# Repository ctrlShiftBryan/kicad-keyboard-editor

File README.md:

# kicad-keyboard-editor README

This is the README for your extension "kicad-keyboard-editor". After writing up a brief description, we recommend including the following sections.

## Features

Describe specific features of your extension including screenshots of your extension in action. Image paths are relative to this README file.

For example if there is an image subfolder under your extension project workspace:

\!\[feature X\]\(images/feature-x.png\)

> Tip: Many popular extensions utilize animations. This is an excellent way to show off your extension! We recommend short, focused animations that are easy to follow.

## Requirements

If you have any requirements or dependencies, add a section describing those and how to install and configure them.

## Extension Settings

Include if your extension adds any VS Code settings through the `contributes.configuration` extension point.

For example:

This extension contributes the following settings:

* `myExtension.enable`: enable/disable this extension
* `myExtension.thing`: set to `blah` to do something

## Known Issues

Calling out known issues can help limit users opening duplicate issues against your extension.

## Release Notes

Users appreciate release notes as you update your extension.

### 1.0.0

Initial release of ...

### 1.0.1

Fixed issue #.

### 1.1.0

Added features X, Y, and Z.

-----------------------------------------------------------------------------------------------------------
## Following extension guidelines

Ensure that you've read through the extensions guidelines and follow the best practices for creating your extension.

* [Extension Guidelines](https://code.visualstudio.com/api/references/extension-guidelines)

## Working with Markdown

**Note:** You can author your README using Visual Studio Code.  Here are some useful editor keyboard shortcuts:

* Split the editor (`Cmd+\` on macOS or `Ctrl+\` on Windows and Linux)
* Toggle preview (`Shift+CMD+V` on macOS or `Shift+Ctrl+V` on Windows and Linux)
* Press `Ctrl+Space` (Windows, Linux) or `Cmd+Space` (macOS) to see a list of Markdown snippets

### For more information

* [Visual Studio Code's Markdown Support](http://code.visualstudio.com/docs/languages/markdown)
* [Markdown Syntax Reference](https://help.github.com/articles/markdown-basics/)

**Enjoy!**

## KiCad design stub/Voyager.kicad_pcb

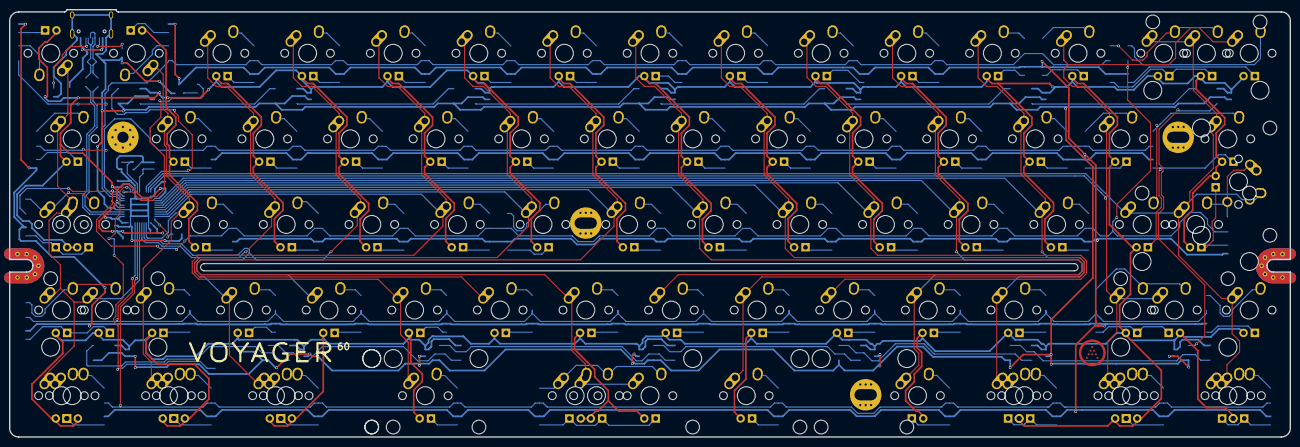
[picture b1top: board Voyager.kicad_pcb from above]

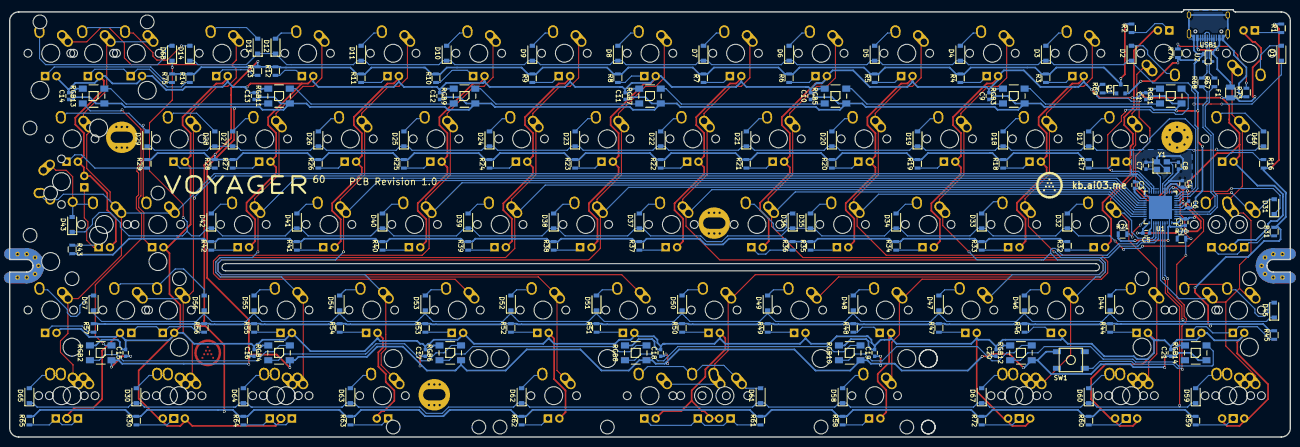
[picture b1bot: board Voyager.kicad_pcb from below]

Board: 2 copper layers, 285.0 x 95.1 mm, 261 parts (181 on the bottom side), 182 nets.

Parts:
C1, C3, C4, C5, C9, C10, C11, C12, C13, C14, C15, C16, C17, C18, C19, C20, C21: 0.1uF; C_0603
C2: 10uF; C_0603
C6: 1uF; C_0603
C7, C8: 22pF; C_0603
D1, D2, D3, D4, D5, D6, D7, D8, D9, D10, D11, D12, D13, D14, D16, D17, D18, D19, D20, D21, D22, D23, D24, D25, D26, D27, D28, D29, D30, D31, D32, D33, D34, D35, D36, D37, D38, D39, D40, D41, D42, D43, D44, D45, D46, D47, D48, D49, D50, D51, D52, D53, D54, D55, D56, D57, D58, D59, D60, D61, D62, D63, D64, D65, D67, D68: SOD-123; D_SOD-123
F1: 500mA; Fuse_SMD1206_Reflow
K_#1, K_#2, K_#3, K_#4, K_#5, K_#6, K_#7, K_#8, K_#9, K_#10: MX-1U
K_'1: MX-1U
K_,1: MX-1U
K_-1: MX-1U
K_.1: MX-1U
K_/1: MX-1U
K_;1: MX-1U
K_=1: MX-1U
K_A1: MX-1U
K_ALT1: MX-1.25U
K_ALT2: MX-1.5U; MX-1.5U-FLIPPED
K_B1: MX-1U
K_BACK1: MX-2U
K_C1: MX-1U
K_CAPS1: MX-1.75U
K_CAPS2: MX-1.25U; MX-1.25U-FLIPPED
K_CTRL1: MX-1.25U
K_CTRL2: MX-1.5U; MX-1.5U-FLIPPED
K_D1: MX-1U
K_E1: MX-1U
K_ENTER1: MX-2.25U
K_ENTER2: MX-ISO; MX-ISO-ReversedStabilizers
K_ESC1: MX-1U
K_F1: MX-1U
K_G1: MX-1U
K_H1: MX-1U
K_I1: MX-1U
K_J1: MX-1U
K_K1: MX-1U
K_L1: MX-1U
K_M1: MX-1U
K_N1: MX-1U
K_O1: MX-1U
K_P1: MX-1U
K_Q1: MX-1U
K_R1: MX-1U
K_RALT2: MX-1.25U; MX-1.25U-FLIPPED
K_RALT3: MX-1.5U; MX-1.5U-FLIPPED
K_RCTRL2: MX-1.25U
K_RCTRL3: MX-1.5U; MX-1.5U-FLIPPED
K_RMENU2: MX-1.25U; MX-1.25U-FLIPPED
K_RSHIFT1: MX-2.75U; MX-2.75U-FLIPPED
K_RWIN2: MX-1.25U
K_RWIN3: MX-1U
K_S1: MX-1U
K_SBACK1, K_SBACK2: MX-1U
K_SHIFT1: MX-2.25U
K_SHIFT2: MX-1.25U
K_SHIFT3: MX-1U
K_SPACE1: MX-7U; MX-7U-ReversedStabilizers
K_SPACE2: MX-6.25U; MX-6.25U-ReversedStabilizers
K_SPACE3: MX-2.25U; MX-2.25U-ReversedStabilizers
K_SPACE4: MX-2.75U; MX-2.75U-ReversedStabilizers
K_SPACE5: MX-1.25U; MX-1.25U-FLIPPED
K_SRSHIFT1: MX-1.75U
K_SRSHIFT2: MX-1U
K_T1: MX-1U
K_TAB1: MX-1.5U
K_U1: MX-1U
K_V1: MX-1U
K_W1: MX-1U
K_WIN1: MX-1.25U
K_WIN2: MX-1U; MX-1U-FLIPPED
K_X1: MX-1U
K_Y1: MX-1U
K_Z1: MX-1U
K_[1: MX-1U
K_\1: MX-1.5U
K_\2: MX-1U
K_]1: MX-1U
Q1: 2N7002; SOT-23
R1, R2, R3, R4, R5, R6, R7, R8, R9, R10, R11, R12, R13, R14, R16, R17, R18, R19, R20, R21, R22, R23, R24, R25, R26, R27, R28, R29, R30, R31, R32, R33, R34, R35, R36, R37, R38, R39, R40, R41, R42, R43, R44, R45, R46, R47, R48, R49, R50, R51, R52, R53, R54, R55, R56, R57, R58, R59, R60, R61, R62, R63, R64, R65, R69, R71, R72, R75: 1k; R_0805
R67, R68: 22; R_0805
R70: 10k; R_0805
R73, R74: 5.1k; R_0805
RGB1, RGB2, RGB3, RGB4, RGB5, RGB6, RGB7, RGB8, RGB9, RGB10, RGB11, RGB12, RGB13, RGB14: WS2812B
SW1: 5.2x5.2mm; SKQG-1155865
U1: ATmega32U4-MU; QFN-44-1EP_7x7mm_Pitch0.5mm
U2: PRTR5V0U2X; SOT143B
USB1: HRO-TYPE-C-31-M-12; HRO-TYPE-C-31-M-12-Assembly
Y1: 16Mhz; Crystal_SMD_3225-4pin_3.2x2.5mm

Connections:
+5V: C1.2, C2.2, C3.2, C4.2, C5.2, C9.2, C10.2, C11.2, C12.2, C13.2, C14.2, C15.2, C16.2, C17.2, C18.2, C19.2, C20.2, C21.2, F1.1, K_#1.3, K_#2.3, K_#3.3, K_#4.3, K_#5.3, K_#6.3, K_#7.3, K_#8.3, K_#9.3, K_#10.3, K_'1.3, K_,1.3, K_-1.3, K_.1.3, K_/1.3, K_;1.3, K_=1.3, K_A1.3, K_ALT1.3, K_ALT2.3, K_B1.3, K_BACK1.3, K_C1.3, K_CAPS1.3, K_CAPS2.3, K_CTRL1.3, K_CTRL2.3, K_D1.3, K_E1.3, K_ENTER1.3, K_ENTER2.3, K_ESC1.3, K_F1.3, K_G1.3, K_H1.3, K_I1.3, K_J1.3, K_K1.3, K_L1.3, K_M1.3, K_N1.3, K_O1.3, K_P1.3, K_Q1.3, K_R1.3, K_RALT2.3, K_RALT3.3, K_RCTRL2.3, K_RCTRL3.3, K_RMENU2.3, K_RSHIFT1.3, K_RWIN2.3, K_RWIN3.3, K_S1.3, K_SBACK1.3, K_SBACK2.3, K_SHIFT1.3, K_SHIFT2.3, K_SHIFT3.3, K_SPACE1.3, K_SPACE2.3, K_SPACE3.3, K_SPACE4.3, K_SPACE5.3, K_SRSHIFT1.3, K_SRSHIFT2.3, K_T1.3, K_TAB1.3, K_U1.3, K_V1.3, K_W1.3, K_WIN1.3, K_WIN2.3, K_X1.3, K_Y1.3, K_Z1.3, K_[1.3, K_\1.3, K_\2.3, K_]1.3, R70.1, RGB1.1, RGB2.1, RGB3.1, RGB4.1, RGB5.1, RGB6.1, RGB7.1, RGB8.1, RGB9.1, RGB10.1, RGB11.1, RGB12.1, RGB13.1, RGB14.1, U1.2, U1.7, U1.14, U1.24, U1.34, U1.44
COL0: K_CAPS1.1, K_CAPS2.2, K_CTRL1.1, K_CTRL2.1, K_ESC1.1, K_SHIFT1.1, K_SHIFT2.1, K_TAB1.1, U1.39
COL1: K_#1.1, K_A1.1, K_Q1.1, K_SHIFT3.1, K_WIN1.1, K_WIN2.1, U1.36
COL2: K_#2.1, K_ALT1.1, K_ALT2.1, K_S1.1, K_W1.1, K_Z1.1, U1.38
COL3: K_#3.1, K_D1.1, K_E1.1, K_X1.1, U1.37
COL4: K_#4.1, K_C1.1, K_F1.1, K_R1.1, K_SPACE3.1, U1.32
COL5: K_#5.1, K_G1.1, K_T1.1, K_V1.1, U1.31
COL6: K_#6.1, K_B1.1, K_H1.1, K_SPACE1.1, K_SPACE2.1, K_SPACE5.2, K_Y1.1, U1.30
COL7: K_#7.1, K_J1.1, K_N1.1, K_U1.1, U1.29
COL8: K_#8.1, K_I1.1, K_K1.1, K_M1.1, K_SPACE4.1, U1.28
COL9: K_#9.1, K_,1.1, K_L1.1, K_O1.1, U1.27
COL10: K_#10.1, K_.1.1, K_;1.1, K_P1.1, K_RALT2.1, U1.26
COL11: K_'1.1, K_-1.1, K_/1.1, K_RALT3.1, K_RWIN2.1, K_[1.1, U1.25
COL12: K_=1.1, K_RMENU2.1, K_RSHIFT1.1, K_RWIN3.1, K_SBACK2.1, K_SRSHIFT1.1, K_]1.1, U1.22
COL13: K_BACK1.1, K_ENTER1.1, K_ENTER2.1, K_RCTRL2.1, K_RCTRL3.1, K_SBACK1.1, K_SRSHIFT2.1, K_\1.1, K_\2.1, U1.21
D+: R68.1, U1.4
D-: R67.1, U1.3
GND: C1.1, C2.1, C3.1, C4.1, C5.1, C6.2, C7.2, C8.2, C9.1, C10.1, C11.1, C12.1, C13.1, C14.1, C15.1, C16.1, C17.1, C18.1, C19.1, C20.1, C21.1, Q1.2, R71.1, R73.1, R74.1, RGB1.3, RGB2.3, RGB3.3, RGB4.3, RGB5.3, RGB6.3, RGB7.3, RGB8.3, RGB9.3, RGB10.3, RGB11.3, RGB12.3, RGB13.3, RGB14.3, SW1.1, U1.5, U1.15, U1.23, U1.35, U1.43, U1.45, U2.1, USB1.1, USB1.12, USB1.13, Y1.2, Y1.4
LEDGND: Q1.3, R1.2, R2.2, R3.2, R4.2, R5.2, R6.2, R7.2, R8.2, R9.2, R10.2, R11.2, R12.2, R13.2, R14.2, R16.2, R17.2, R18.2, R19.2, R20.2, R21.2, R22.2, R23.2, R24.2, R25.2, R26.2, R27.2, R28.2, R29.2, R30.2, R31.2, R32.2, R33.2, R34.2, R35.2, R36.2, R37.2, R38.2, R39.2, R40.2, R41.2, R42.2, R43.2, R44.2, R45.2, R46.2, R47.2, R48.2, R49.2, R50.2, R51.2, R52.2, R53.2, R54.2, R55.2, R56.2, R57.2, R58.2, R59.2, R60.2, R61.2, R62.2, R63.2, R64.2, R65.2, R72.2, R75.2
unnamed: C6.1, U1.6
unnamed: C7.1, U1.17, Y1.1
unnamed: C8.1, U1.16, Y1.3
unnamed: D1.2, K_ESC1.2
unnamed: D2.2, K_#1.2
unnamed: D3.2, K_#2.2
unnamed: D4.2, K_#3.2
unnamed: D5.2, K_#4.2
unnamed: D6.2, K_#5.2
unnamed: D7.2, K_#6.2
unnamed: D8.2, K_#7.2
unnamed: D9.2, K_#8.2
unnamed: D10.2, K_#9.2
unnamed: D11.2, K_#10.2
unnamed: D12.2, K_-1.2
unnamed: D13.2, K_=1.2
unnamed: D14.2, K_BACK1.2, K_SBACK1.2
unnamed: D16.2, K_TAB1.2
unnamed: D17.2, K_Q1.2
unnamed: D18.2, K_W1.2
unnamed: D19.2, K_E1.2
unnamed: D20.2, K_R1.2
unnamed: D21.2, K_T1.2
unnamed: D22.2, K_Y1.2
unnamed: D23.2, K_U1.2
unnamed: D24.2, K_I1.2
unnamed: D25.2, K_O1.2
unnamed: D26.2, K_P1.2
unnamed: D27.2, K_[1.2
unnamed: D28.2, K_]1.2
unnamed: D29.2, K_\1.2, K_\2.2
unnamed: D30.2, K_RMENU2.2, K_RWIN3.2
unnamed: D31.2, K_CAPS1.2, K_CAPS2.1
unnamed: D32.2, K_A1.2
unnamed: D33.2, K_S1.2
unnamed: D34.2, K_D1.2
unnamed: D35.2, K_F1.2
unnamed: D36.2, K_G1.2
unnamed: D37.2, K_H1.2
unnamed: D38.2, K_J1.2
unnamed: D39.2, K_K1.2
unnamed: D40.2, K_L1.2
unnamed: D41.2, K_;1.2
unnamed: D42.2, K_'1.2
unnamed: D43.2, K_ENTER1.2, K_ENTER2.2
unnamed: D44.2, K_SHIFT3.2
unnamed: D45.2, K_SHIFT1.2, K_SHIFT2.2
unnamed: D46.2, K_Z1.2
unnamed: D47.2, K_X1.2
unnamed: D48.2, K_C1.2
unnamed: D49.2, K_V1.2
unnamed: D50.2, K_B1.2
unnamed: D51.2, K_N1.2
unnamed: D52.2, K_M1.2
unnamed: D53.2, K_,1.2
unnamed: D54.2, K_.1.2
unnamed: D55.2, K_/1.2
unnamed: D56.2, K_RSHIFT1.2, K_SRSHIFT1.2
unnamed: D57.2, K_SRSHIFT2.2
unnamed: D58.2, K_SPACE3.2
unnamed: D59.2, K_CTRL1.2, K_CTRL2.2
unnamed: D60.2, K_WIN1.2, K_WIN2.2
unnamed: D61.2, K_SPACE1.2, K_SPACE2.2, K_SPACE5.1
unnamed: D62.2, K_SPACE4.2
unnamed: D63.2, K_RALT2.2
unnamed: D64.2, K_RALT3.2, K_RWIN2.2
unnamed: D65.2, K_RCTRL2.2, K_RCTRL3.2
unnamed: D67.2, K_ALT1.2, K_ALT2.2
unnamed: D68.2, K_SBACK2.2
unnamed: K_#1.4, R2.1
unnamed: K_#2.4, R3.1
unnamed: K_#3.4, R4.1
unnamed: K_#4.4, R5.1
unnamed: K_#5.4, R6.1
unnamed: K_#6.4, R7.1
unnamed: K_#7.4, R8.1
unnamed: K_#8.4, R9.1
unnamed: K_#9.4, R10.1
unnamed: K_#10.4, R11.1
unnamed: K_'1.4, R42.1
unnamed: K_,1.4, R53.1
unnamed: K_-1.4, R12.1
unnamed: K_.1.4, R54.1
unnamed: K_/1.4, R55.1
unnamed: K_;1.4, R41.1
unnamed: K_=1.4, R13.1
unnamed: K_A1.4, R32.1
unnamed: K_ALT1.4, K_ALT2.4, R72.1
unnamed: K_B1.4, R50.1
unnamed: K_BACK1.4, K_SBACK1.4, R14.1
unnamed: K_C1.4, R48.1
unnamed: K_CAPS1.4, K_CAPS2.4, R31.1
unnamed: K_CTRL1.4, K_CTRL2.4, R59.1
unnamed: K_D1.4, R34.1
unnamed: K_E1.4, R19.1
unnamed: K_ENTER1.4, K_ENTER2.4, R43.1
unnamed: K_ESC1.4, R1.1
unnamed: K_F1.4, R35.1
unnamed: K_G1.4, R36.1
unnamed: K_H1.4, R37.1
unnamed: K_I1.4, R24.1
unnamed: K_J1.4, R38.1
unnamed: K_K1.4, R39.1
unnamed: K_L1.4, R40.1
unnamed: K_M1.4, R52.1
unnamed: K_N1.4, R51.1
unnamed: K_O1.4, R25.1
unnamed: K_P1.4, R26.1
unnamed: K_Q1.4, R17.1
unnamed: K_R1.4, R20.1
unnamed: K_RALT2.4, R63.1
unnamed: K_RALT3.4, K_RWIN2.4, R64.1
unnamed: K_RCTRL2.4, K_RCTRL3.4, R65.1
unnamed: K_RMENU2.4, K_RWIN3.4, R30.1
unnamed: K_RSHIFT1.4, K_SRSHIFT1.4, R56.1
unnamed: K_S1.4, R33.1
unnamed: K_SBACK2.4, R75.1
unnamed: K_SHIFT1.4, K_SHIFT2.4, R45.1
unnamed: K_SHIFT3.4, R44.1
unnamed: K_SPACE1.4, K_SPACE2.4, K_SPACE5.4, R61.1
unnamed: K_SPACE3.4, R58.1
unnamed: K_SPACE4.4, R62.1
unnamed: K_SRSHIFT2.4, R57.1
unnamed: K_T1.4, R21.1
unnamed: K_TAB1.4, R16.1
unnamed: K_U1.4, R23.1
unnamed: K_V1.4, R49.1
unnamed: K_W1.4, R18.1
unnamed: K_WIN1.4, K_WIN2.4, R60.1
unnamed: K_X1.4, R47.1
unnamed: K_Y1.4, R22.1
unnamed: K_Z1.4, R46.1
unnamed: K_[1.4, R27.1
unnamed: K_\1.4, K_\2.4, R29.1
unnamed: K_]1.4, R28.1
unnamed: Q1.1, R69.1
unnamed: R67.2, U2.3, USB1.5, USB1.7
unnamed: R68.2, U2.2, USB1.6, USB1.8
unnamed: R69.2, U1.12
unnamed: R70.2, SW1.2, U1.13
unnamed: R71.2, U1.33
unnamed: R73.2, USB1.4
unnamed: R74.2, USB1.10
unnamed: RGB1.2, RGB3.4
unnamed: RGB2.2, RGB4.4
unnamed: RGB3.2, RGB5.4
unnamed: RGB4.2, RGB6.4
unnamed: RGB5.2, RGB7.4
unnamed: RGB6.2, RGB8.4
unnamed: RGB7.2, RGB9.4
unnamed: RGB10.2, RGB12.4
unnamed: RGB8.2, RGB10.4
unnamed: RGB11.2, RGB13.4
unnamed: RGB9.2, RGB11.4
unnamed: RGB12.2, RGB14.4
unnamed: RGB2.4, RGB13.2
RGBLED: RGB1.4, U1.20
ROW0: D1.1, D2.1, D3.1, D4.1, D5.1, D6.1, D7.1, D8.1, D9.1, D10.1, D11.1, D12.1, D13.1, D14.1, U1.9
ROW1: D16.1, D17.1, D18.1, D19.1, D20.1, D21.1, D22.1, D23.1, D24.1, D25.1, D26.1, D27.1, D28.1, D29.1, U1.10
ROW2: D31.1, D32.1, D33.1, D34.1, D35.1, D36.1, D37.1, D38.1, D39.1, D40.1, D41.1, D42.1, D43.1, D68.1, U1.11
ROW3: D44.1, D45.1, D46.1, D47.1, D48.1, D49.1, D50.1, D51.1, D52.1, D53.1, D54.1, D55.1, D56.1, D57.1, U1.41
ROW4: D30.1, D58.1, D59.1, D60.1, D61.1, D62.1, D63.1, D64.1, D65.1, D67.1, U1.40
VCC: F1.2, U2.4, USB1.2, USB1.11

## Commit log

2021-04-13 init
2021-04-13 setup jest and parser
